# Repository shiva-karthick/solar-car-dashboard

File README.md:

# Singapore Polytechnic SunSPEC 6 solar vehicle

### An Example of the car dashboard

Instructions

```bash
sudo pip install pyserial
sudo pip install pygame
```

### Ideas

- Data from solar car as blockchain
- Solar Car Fault prediction
- Lattepanda and pyfirmata
- Raspberry pi and Arduino Mega
- Arduino Tachometer(IR sensor, hall effect sensor and magnet reed switch) and FPGA

Related Links:
[SunSPEC in Singapore Polytechnic Engineering Show](http://spengineeringshow.sp.edu.sg/2018/CB15EM/)

[SunSPEC 6 FYP Team](https://shankar-shiv.github.io/solar-car-blog/)

[SunSPEC 5 Battery](https://batterysunspec5.wordpress.com/)

[SunSPEC 5 Telemetry blog](http://telemetry-sunspec5.blogspot.com/)

[SunSPEC 4 Telemetry blog](http://sunspec4-telemetry.blogspot.com/)

Copyright 2018 Shankar

Licensed under the Apache License, Version 2.0 (the "License");
you may not use this file except in compliance with the License.
You may obtain a copy of the License at

       http://www.apache.org/licenses/LICENSE-2.0

Unless required by applicable law or agreed to in writing, software
distributed under the License is distributed on an "AS IS" BASIS,
WITHOUT WARRANTIES OR CONDITIONS OF ANY KIND, either express or implied.
See the License for the specific language governing permissions and
limitations under the License.

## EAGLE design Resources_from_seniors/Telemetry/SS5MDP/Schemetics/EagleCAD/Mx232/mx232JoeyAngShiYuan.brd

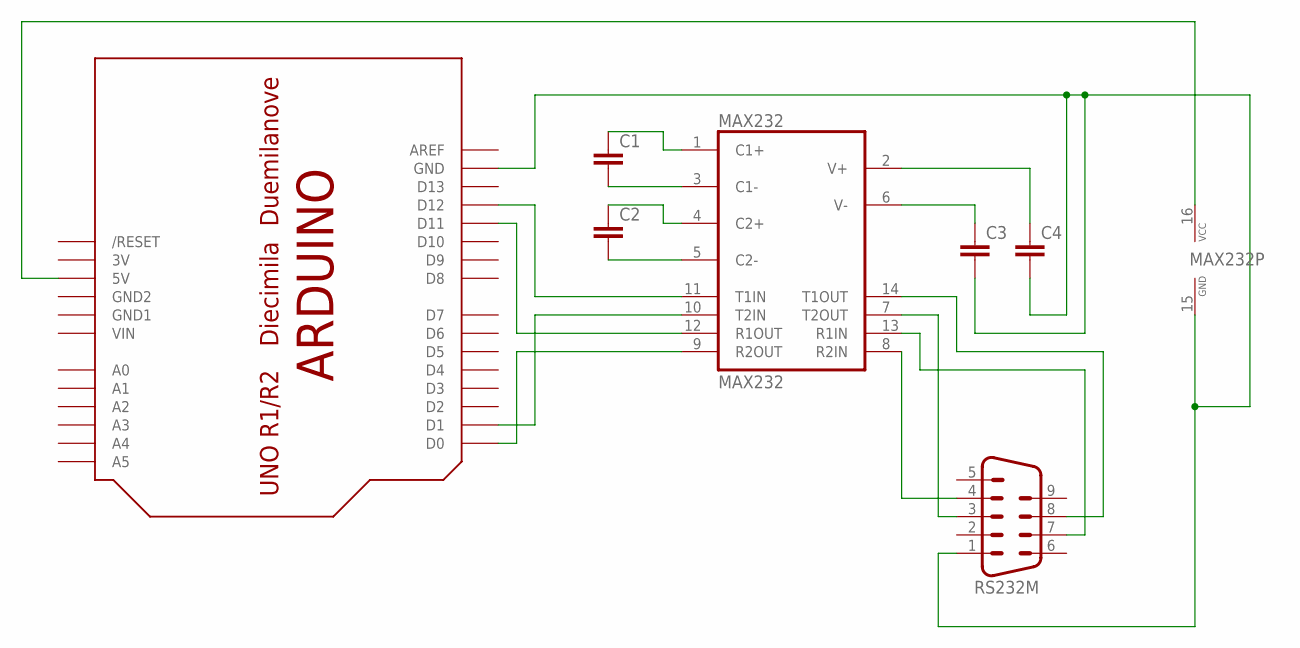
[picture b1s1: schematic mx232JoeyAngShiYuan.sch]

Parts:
C1, C2, C3, C4: C2,5-3; C2.5-3
LEONARDO-SHIELD: ARDUINO-NOHOLE
MAX232: MAX232; DIL16
RS232M: M09HP

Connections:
3V: LEONARDO-SHIELD.3V
GND1: LEONARDO-SHIELD.GND1
GND2: LEONARDO-SHIELD.GND2
unnamed: LEONARDO-SHIELD.D11, MAX232.12 (R1OUT)
unnamed: LEONARDO-SHIELD.D0, MAX232.9 (R2OUT)
unnamed: LEONARDO-SHIELD.D1, MAX232.10 (T2IN)
unnamed: LEONARDO-SHIELD.D12, MAX232.11 (T1IN)
unnamed: C1.1, MAX232.1 (C1+)
unnamed: C1.2, MAX232.3 (C1-)
unnamed: C2.1, MAX232.4 (C2+)
unnamed: C2.2, MAX232.5 (C2-)
unnamed: C4.1, MAX232.2 (V+)
unnamed: C3.1, MAX232.6 (V-)
unnamed: C3.2, C4.2, LEONARDO-SHIELD.GND, MAX232.15 (GND), RS232M.1
unnamed: LEONARDO-SHIELD.5V, MAX232.16 (VCC)
unnamed: MAX232.14 (T1OUT), RS232M.8
unnamed: MAX232.7 (T2OUT), RS232M.3
unnamed: MAX232.13 (R1IN), RS232M.7
unnamed: MAX232.8 (R2IN), RS232M.4
VIN: LEONARDO-SHIELD.VIN

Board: 2 copper layers, 7 parts (0 on the bottom side), 16 nets, no tracks yet.

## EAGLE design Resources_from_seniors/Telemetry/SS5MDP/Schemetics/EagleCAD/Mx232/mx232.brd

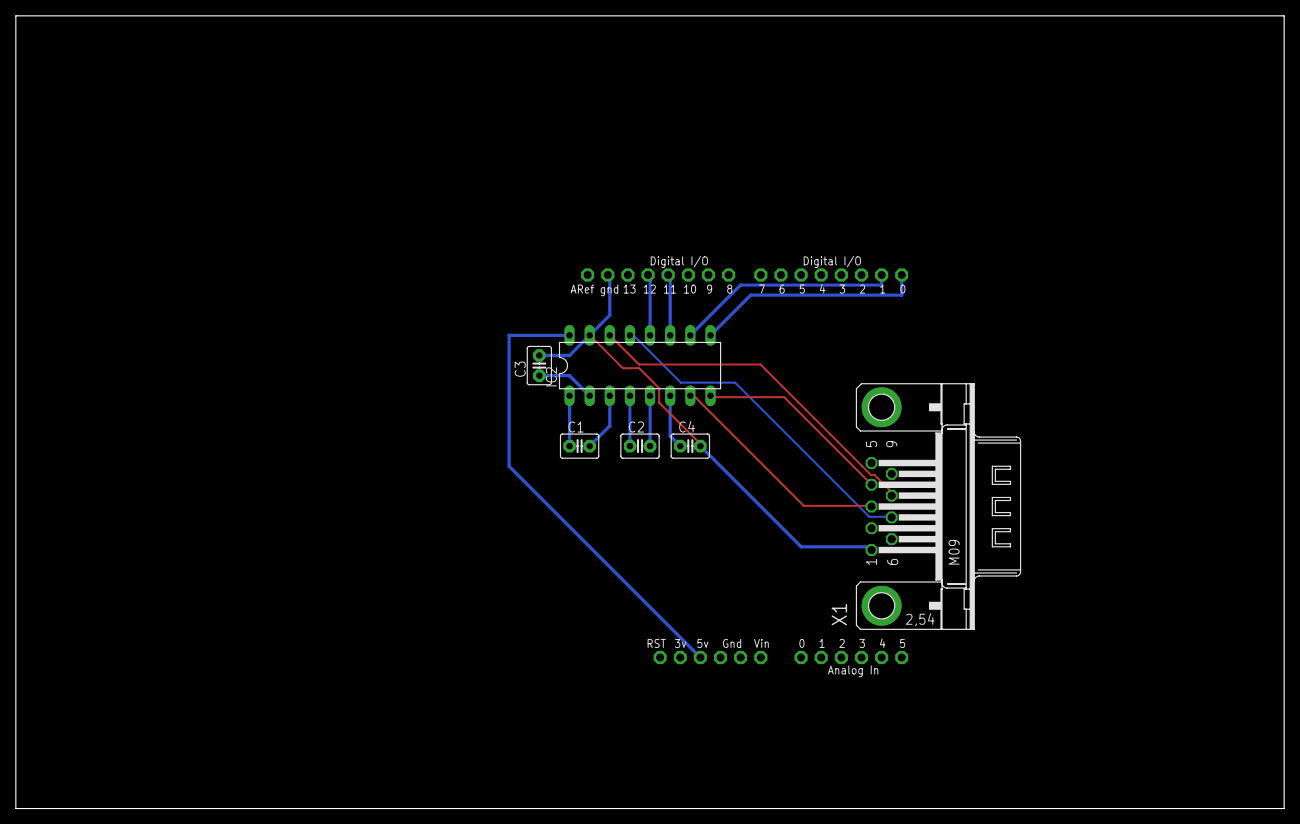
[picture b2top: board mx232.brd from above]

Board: 2 copper layers, 160.0 x 100.0 mm, 7 parts (0 on the bottom side), 16 nets.

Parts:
C1, C2, C3, C4: C2.5-3
IC2: MAX232; DIL16
U$1: ARDUINO-NOHOLE
X1: M09HP

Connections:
unnamed: IC2.12, U$1.D12
unnamed: IC2.9, U$1.D0
unnamed: IC2.10, U$1.D1
unnamed: IC2.11, U$1.D11
unnamed: C1.1, IC2.1
unnamed: C1.2, IC2.3
unnamed: C2.1, IC2.4
unnamed: C2.2, IC2.5
unnamed: C3.1, IC2.2
unnamed: C4.1, IC2.6
unnamed: C3.2, C4.2, IC2.15, U$1.GND, X1.1
unnamed: IC2.16, U$1.5V
unnamed: IC2.14, X1.8
unnamed: IC2.7, X1.3
unnamed: IC2.13, X1.7
unnamed: IC2.8, X1.4

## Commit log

2018-06-09 Initial update
2018-06-18 Design done
2018-06-18 uploaded senior's program files
    These files are from our senior Joey, lot's of example are there, please take a look !
2018-06-19 i am testing 1...2...3...
2018-06-19 Speedometer first arc drawing test successfully done
2018-06-19 speedometer test 2 done successfully ! much better now 1km/h = 1.205 degrees
2018-06-21 Battery test successfully completed
2018-06-24 Temperature done ! and DHT 22 sensor also tested !
2018-06-24 Draft 2 program working well!
2018-06-24 draft 3 successfully done ! All 3 components Speedometer, Battery and Temperature are completed
2018-06-28 camera test 1 done
2018-06-28 Updated License.txt
2018-07-18 Dashboard with Windows support completed!
2018-07-18 Added some helpful comments
2018-07-19 demos from raspberry pi added to main repo
2018-07-19 running C# for the first time ! C# is awesome!
2018-07-21 Battery arc and speedometer arc demos successfully completed, only left camera and battery
2018-07-27 Able to make GPS work with the help of Jian Kun and other changes
    + GPS working
    + 2nd draft done (Battery not yet done)
    + Backup files included
    + Adafruit GPS logger shield datasheet included + highlighted version
    +
2018-07-27 battery part written haven't tested out yet LOL
    + Some organising of files
2018-07-28 Added a version of highlighted Ultimate-GPS-logger-shield-PDF file
2018-08-02 Commit using Visual Studio is damn cool!!!!! Battery.ino added
2018-08-02 Demo to push to Github via Visual Studio
2018-08-30 PLX DAQ related files added
2018-09-10 minor changes
2018-09-10 Minor Fixes
    Added pyserial documentation.pdf file
2018-09-12 Draft of the whole program getting ready and minor fixes
2018-09-18 Draft 5 added with almost complete set of program done
    The GUI is almost done at draft5.py
2018-09-19 draft4 which is the main file is updated. See description for details
    draft4 is updated with battery warning sign and colour of the battery (green, yellow, red) is also added
2018-09-25 Battery dashboard successfully tested with His grace
2018-09-30 final bug fixes in draft4.py
2018-09-30 lora successfull tested, its simple just configure using the RF module manager, and just use PLX-DAQ code to transmit and it will receive automatically
2018-10-01 lora pdf updated
2018-10-08 Added lora + GUI integration support thx Guru
2018-10-08 added the lora and GUI successfull integration
2018-10-09 battery warning lightning symbol added
    + fixed some battery red, yellow , green colour changing bugs
    + need to add 5 current sensors implementation
2018-11-07 7 sensors support added, organised arduino files, thx
2018-11-15 Finished whole set of arduino program for the dashboard need to test the arduino program
2018-11-18 Completed draft3.ino need to teston actual hardware, need to do a complete test and also squah all the bugs
2018-11-18 fixed bugs in draft3.ino
2018-12-01 added machine learning, fpga folders and grouped lattepanda and raspberry pi separately, dont freak out arduino code and other datasheets are in the raspberry pi folder
2018-12-10 Reorganised a few things and started working on the lattepanda version
2018-12-11 Going crazy of how to connect lattepanda to python program
2018-12-11 refactored draft4.py and rearranged a few folders
2018-12-11 Successfully completed Open CV camera embedded in pygame surface
2018-12-12 lattepanda gui and open_cv tested successfully but LoRa cannot work :)
2018-12-18 Successfully Completed all tests of lattepanda; ready to deploy :)
2018-12-24 finally completed lattepanda Sensor final draft4, works OK
2019-01-04 Set theme jekyll-theme-cayman
2019-01-05 finally all problems resolved lesson learnt : DO NOT UPLOAD HUGE FILES!
2019-01-05 added my SunSPEC blog
2019-01-05 struggling to build a website
2019-01-05 finally finished up blog whew!!!
2019-01-05 Set theme jekyll-theme-architect
2019-01-05 cannot view the site in github
2019-01-05 cannot view the site in github, so trying again
2019-01-05 cannot view the site in github, so trying again, trying again!!!
2019-01-05 cannot view the site in github, so trying again, trying again!!! again
2019-01-05 DO NOT touch this repo frequently
2019-01-05 removed the docs folder
2019-01-12 added example interrupts arduino file
2019-01-17 added some tachometer files and lora-test-data, magnet for tachometer
2020-05-22 cleaned up junk
